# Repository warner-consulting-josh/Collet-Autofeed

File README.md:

# Collet-Autofeed

Automation of Collets on the Tormach Slant Pro lathe using a custom tooling block, individually addressable coolant lines controlled by an [UnexpectedMaker ProS3](https://esp32s3.com/pros3.html) and ui_hooks.py, and custom G-code for auto stock advance.

## Description

This project uses the uihooks.py [Plugin controller](http://xoomspeed.com/CNC/pathpilot/plugins/uihooks.htm) created by David Loomes at XoomSpeed, to run custom python code for interacting with a ProS3 microcontroller which in turn controls solenoids to direct the coolant stream to the currently active tool. We've also implemented custom G-code to auto advance the stock after each part with a GUI for inputting the stock length at the beginning of the run. (The stock input GUI only works on earlier versions of PathPilot, but it is not reequired for the rest of the system to function)
The hardware includes a custom tooling block, a manifold for the solenoids, a main board with the microcontroller and relays, a connector board to break out the relay lines, and enclosures for both boards.

## Getting Started

### Dependencies

* PathPilot V2
* PathPilot Plugins by [Xoomspeed](http://xoomspeed.com/CNC/pathpilot/plugins.htm)

### Installing

* Follow the instructions from [Xoomspeed](http://xoomspeed.com/CNC/pathpilot/plugins.htm) for intstalling the PathPilot Plugin framework
   * The specific plugin for running the coolant controller is [here:](https://github.com/warner-consulting-josh/Collet-Autofeed/blob/main/PathPilot%20Python/ProS3Cool_plugin.py)
* The circuitpython code that runs on the microcontroller is [here:](https://github.com/warner-consulting-josh/Collet-Autofeed/blob/main/ProS3%20CircuitPython/code.py)
   * Note that the file must be named code.py for the microcontroller using circuitpython to recognize and run it 

### Circuit Boards

* Gerber files for ordering the circuit boards are [here:](https://github.com/warner-consulting-josh/Collet-Autofeed/tree/main/KiCAD/Addressable_Coolant_Controller/gerber_to_order)
* boards were designed in KiCAD using a multi-board workflow with [KiKit](https://yaqwsx.github.io/KiKit/v1.4/multiboard/)

## Authors

Contributors names and contact info

Josh Warner  
joshua@warner-consulting.com

## Version History

* 1.0.0
    * Initial Release

## License

This project is licensed under the [GPL-3.0-only](https://opensource.org/license/gpl-3-0) License

## Acknowledgments

Inspiration, code snippets, etc.
* [XoomSpeed](http://xoomspeed.com/index.htm)
* [KiKit](https://yaqwsx.github.io/KiKit/v1.4/)
* [awesome-readme](https://github.com/matiassingers/awesome-readme)
* [PurpleBooth](https://gist.github.com/PurpleBooth/109311bb0361f32d87a2)
* [dbader](https://github.com/dbader/readme-template)
* [zenorocha](https://gist.github.com/zenorocha/4526327)
* [fvcproductions](https://gist.github.com/fvcproductions/1bfc2d4aecb01a834b46)

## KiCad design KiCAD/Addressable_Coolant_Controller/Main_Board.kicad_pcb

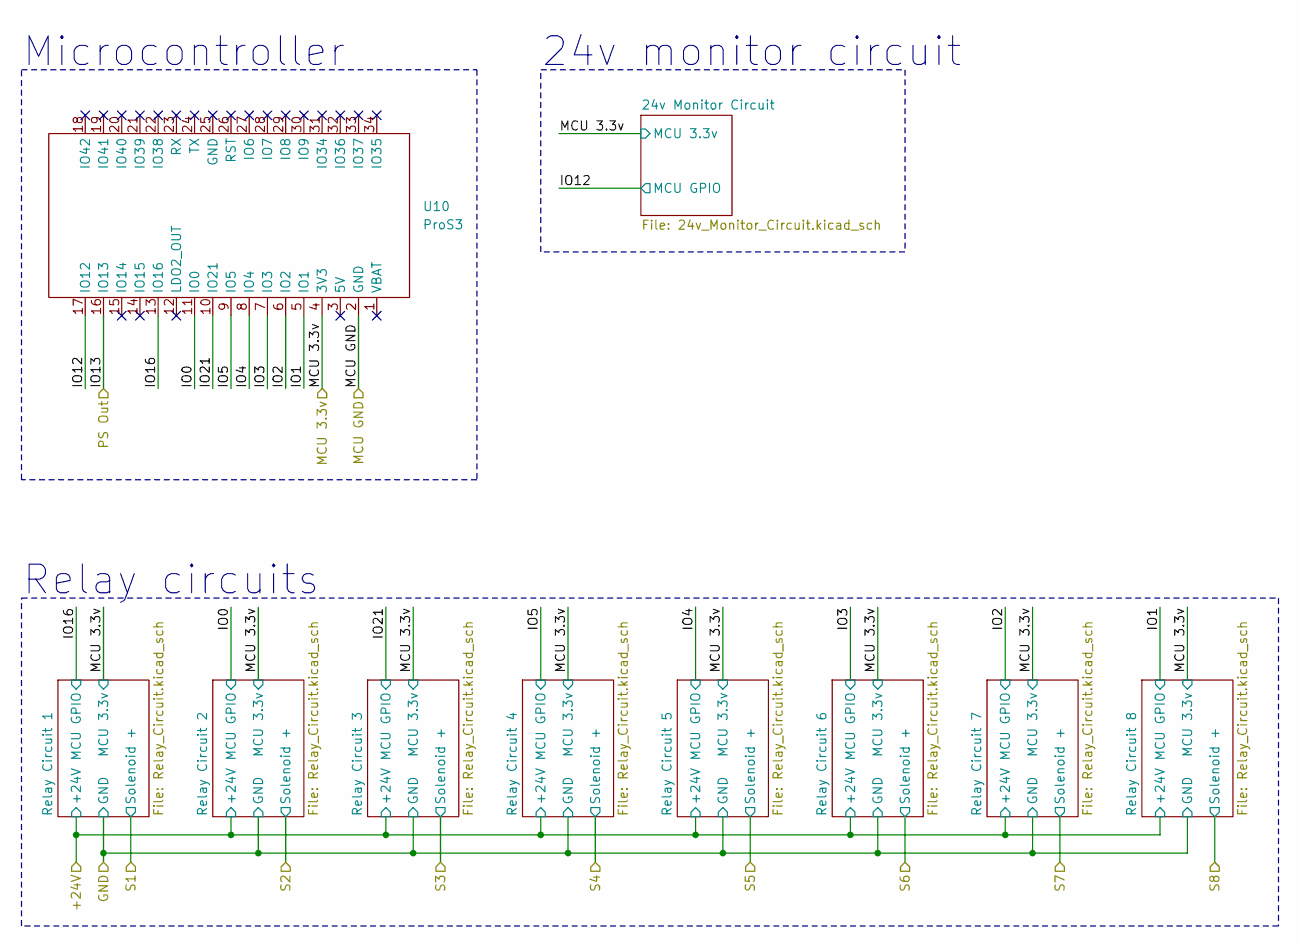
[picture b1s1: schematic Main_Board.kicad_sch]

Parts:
U10: ProS3; ProS3_TH

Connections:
/Main_Board/IO0: U10.11 (IO0); also elsewhere on the board
/Main_Board/IO1: U10.5 (IO1); also elsewhere on the board
/Main_Board/IO2: U10.6 (IO2); also elsewhere on the board
/Main_Board/IO3: U10.7 (IO3); also elsewhere on the board
/Main_Board/IO4: U10.8 (IO4); also elsewhere on the board
/Main_Board/IO5: U10.9 (IO5); also elsewhere on the board
/Main_Board/IO12: U10.17 (IO12); also elsewhere on the board
/Main_Board/IO13: U10.16 (IO13); also elsewhere on the board
/Main_Board/IO16: U10.13 (IO16); also elsewhere on the board
/Main_Board/IO21: U10.10 (IO21); also elsewhere on the board
/Main_Board/MCU 3.3v: U10.4 (3V3); also elsewhere on the board
/Main_Board/MCU GND: U10.2 (GND); also elsewhere on the board

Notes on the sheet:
Microcontroller
24v monitor circuit
Relay circuits

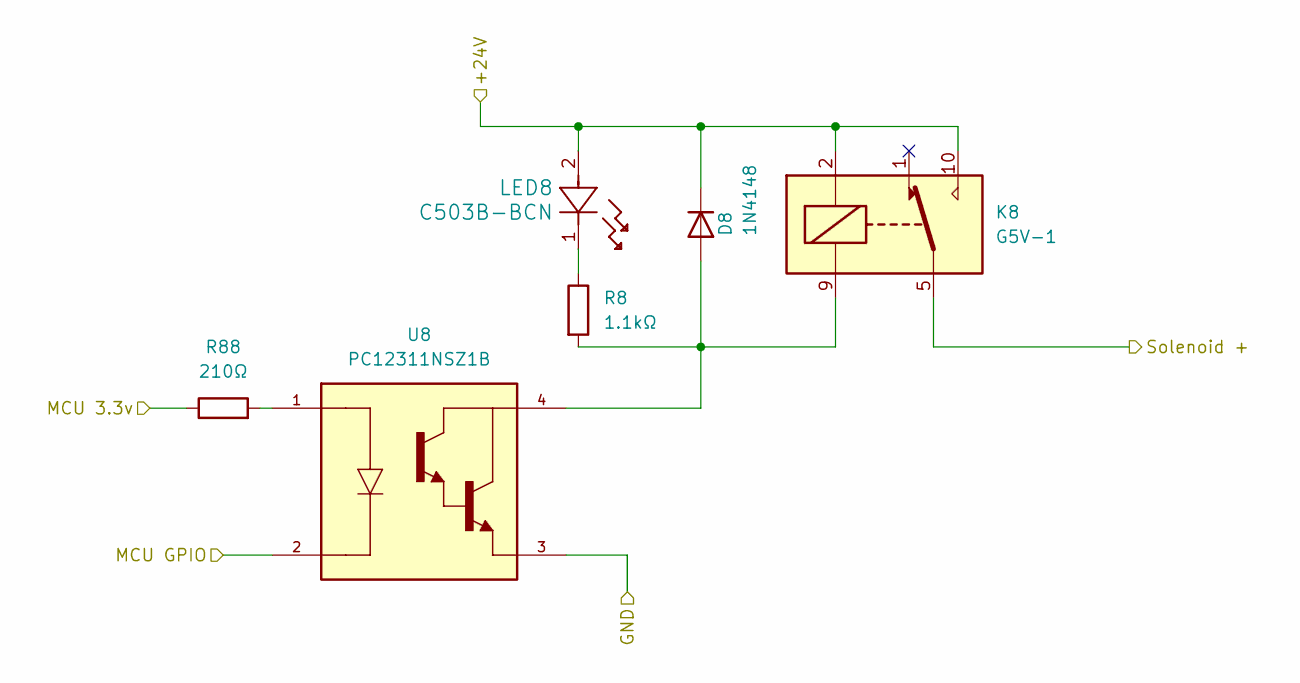
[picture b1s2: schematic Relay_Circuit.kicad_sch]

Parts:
D8: 1N4148; D_DO-35_SOD27_P7.62mm_Horizontal-JW
K8: G5V-1; Relay_SPDT_Omron_G5V-1
LED8: C503B-BCN; C503B_BCN_CV0Z0461
R8: 1.1kΩ; R_Axial_DIN0204_L3.6mm_D1.6mm_P5.08mm_Horizontal-JW
R88: 210Ω; R_Axial_DIN0204_L3.6mm_D1.6mm_P5.08mm_Horizontal-JW
U8: PC12311NSZ1B; Mouser Part Number 852-PC12311NSZ1B

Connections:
+24V: D8.1 (K), K8.2, K8.10, LED8.2; also elsewhere on the board
/Main_Board/IO1: U8.2; also elsewhere on the board
/Main_Board/MCU 3.3v: R88.1; also elsewhere on the board
/Main_Board/S8: K8.5, K8.6; also elsewhere on the board
GND: U8.3; also elsewhere on the board
unnamed: D8.2 (A), K8.9, R8.2, U8.4
unnamed: LED8.1, R8.1
unnamed: R88.2, U8.1

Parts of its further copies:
D1, D2, D3, D4, D5, D6, D7: 1N4148; D_DO-35_SOD27_P7.62mm_Horizontal-JW
K1, K2, K3, K4, K5, K6, K7: G5V-1; Relay_SPDT_Omron_G5V-1
LED1, LED2, LED3, LED4, LED5, LED6, LED7: C503B-BCN; C503B_BCN_CV0Z0461
R1, R2, R3, R4, R5, R6, R7: 1.1kΩ; R_Axial_DIN0204_L3.6mm_D1.6mm_P5.08mm_Horizontal-JW
R11, R22, R33, R44, R55, R66, R77: 210Ω; R_Axial_DIN0204_L3.6mm_D1.6mm_P5.08mm_Horizontal-JW
U1, U2, U3, U4, U5, U6, U7: PC12311NSZ1B; Mouser Part Number 852-PC12311NSZ1B

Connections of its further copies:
+24V: D1.1 (K), D2.1 (K), D3.1 (K), D4.1 (K), D5.1 (K), D6.1 (K), D7.1 (K), K1.2, K1.10, K2.2, K2.10, K3.2, K3.10, K4.2, K4.10, K5.2, K5.10, K6.2, K6.10, K7.2, K7.10, LED1.2, LED2.2, LED3.2, LED4.2, LED5.2, LED6.2, LED7.2; also elsewhere on the board
/Main_Board/IO0: U2.2; also elsewhere on the board
/Main_Board/IO2: U7.2; also elsewhere on the board
/Main_Board/IO3: U6.2; also elsewhere on the board
/Main_Board/IO4: U5.2; also elsewhere on the board
/Main_Board/IO5: U4.2; also elsewhere on the board
/Main_Board/IO16: U1.2; also elsewhere on the board
/Main_Board/IO21: U3.2; also elsewhere on the board
/Main_Board/MCU 3.3v: R11.1, R22.1, R33.1, R44.1, R55.1, R66.1, R77.1; also elsewhere on the board
/Main_Board/S1: K1.5, K1.6; also elsewhere on the board
/Main_Board/S2: K2.5, K2.6; also elsewhere on the board
/Main_Board/S3: K3.5, K3.6; also elsewhere on the board
/Main_Board/S4: K4.5, K4.6; also elsewhere on the board
/Main_Board/S5: K5.5, K5.6; also elsewhere on the board
/Main_Board/S6: K6.5, K6.6; also elsewhere on the board
/Main_Board/S7: K7.5, K7.6; also elsewhere on the board
GND: U1.3, U2.3, U3.3, U4.3, U5.3, U6.3, U7.3; also elsewhere on the board
unnamed: D1.2 (A), K1.9, R1.2, U1.4
unnamed: D2.2 (A), K2.9, R2.2, U2.4
unnamed: D3.2 (A), K3.9, R3.2, U3.4
unnamed: D4.2 (A), K4.9, R4.2, U4.4
unnamed: D5.2 (A), K5.9, R5.2, U5.4
unnamed: D6.2 (A), K6.9, R6.2, U6.4
unnamed: D7.2 (A), K7.9, R7.2, U7.4
unnamed: LED1.1, R1.1
unnamed: LED2.1, R2.1
unnamed: LED3.1, R3.1
unnamed: LED4.1, R4.1
unnamed: LED5.1, R5.1
unnamed: LED6.1, R6.1
unnamed: LED7.1, R7.1
unnamed: R11.2, U1.1
unnamed: R22.2, U2.1
unnamed: R33.2, U3.1
unnamed: R44.2, U4.1
unnamed: R55.2, U5.1
unnamed: R66.2, U6.1
unnamed: R77.2, U7.1

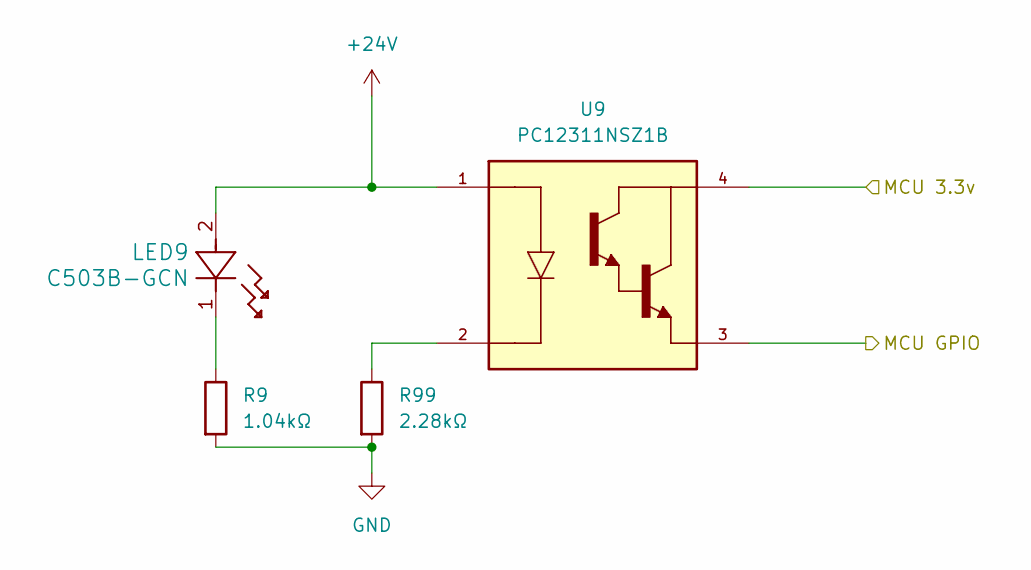
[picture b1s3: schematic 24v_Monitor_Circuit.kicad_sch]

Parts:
LED9: C503B-GCN; C503B_GCN_CY0C0792
R9: 1.04kΩ; R_Axial_DIN0204_L3.6mm_D1.6mm_P5.08mm_Horizontal-JW
R99: 2.28kΩ; R_Axial_DIN0204_L3.6mm_D1.6mm_P5.08mm_Horizontal-JW
U9: PC12311NSZ1B; Mouser Part Number 852-PC12311NSZ1B

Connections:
+24V: LED9.2, U9.1; also elsewhere on the board
/Main_Board/IO12: U9.3; also elsewhere on the board
/Main_Board/MCU 3.3v: U9.4; also elsewhere on the board
GND: R9.2, R99.2; also elsewhere on the board
unnamed: LED9.1, R9.1
unnamed: R99.1, U9.2

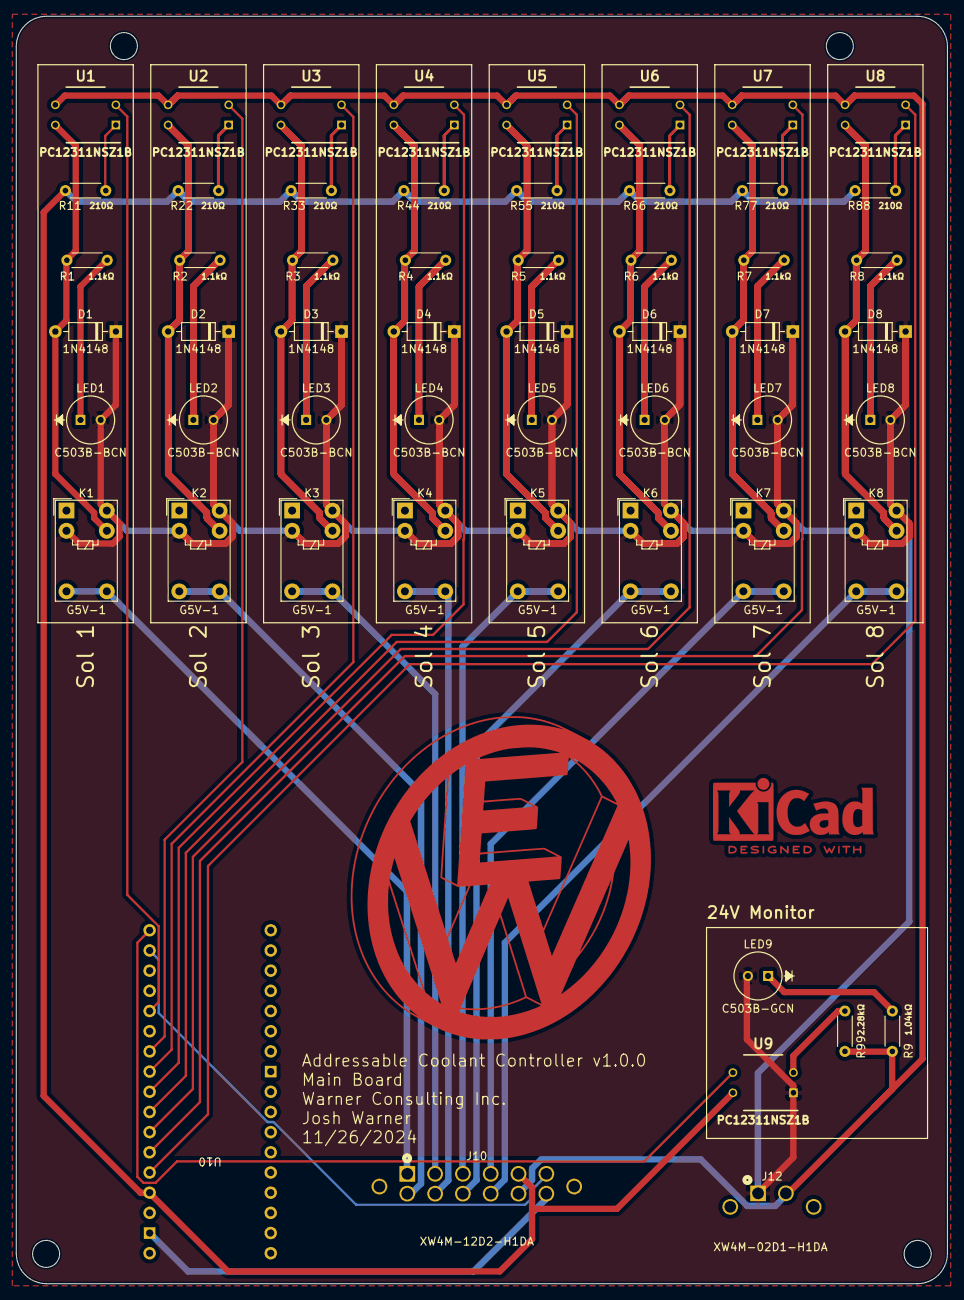
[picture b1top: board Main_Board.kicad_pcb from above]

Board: 2 copper layers, 117.2 x 159.5 mm, 56 parts (0 on the bottom side), 48 nets.

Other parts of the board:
J10: XW4M-12D2-H1DA; xw4m-12d2-h1da
J12: XW4M-02D1-H1DA; xw4m-02d1-h1da
Main_Board: Board

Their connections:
+24V: J12.1; also elsewhere on the board
/Main_Board/IO13: J10.6; also elsewhere on the board
/Main_Board/MCU 3.3v: J10.5; also elsewhere on the board
/Main_Board/MCU GND: J10.12; also elsewhere on the board
/Main_Board/S1: J10.1; also elsewhere on the board
/Main_Board/S2: J10.7; also elsewhere on the board
/Main_Board/S3: J10.2; also elsewhere on the board
/Main_Board/S4: J10.8; also elsewhere on the board
/Main_Board/S5: J10.3; also elsewhere on the board
/Main_Board/S6: J10.9; also elsewhere on the board
/Main_Board/S7: J10.4; also elsewhere on the board
/Main_Board/S8: J10.10; also elsewhere on the board
GND: J10.11, J12.2; also elsewhere on the board

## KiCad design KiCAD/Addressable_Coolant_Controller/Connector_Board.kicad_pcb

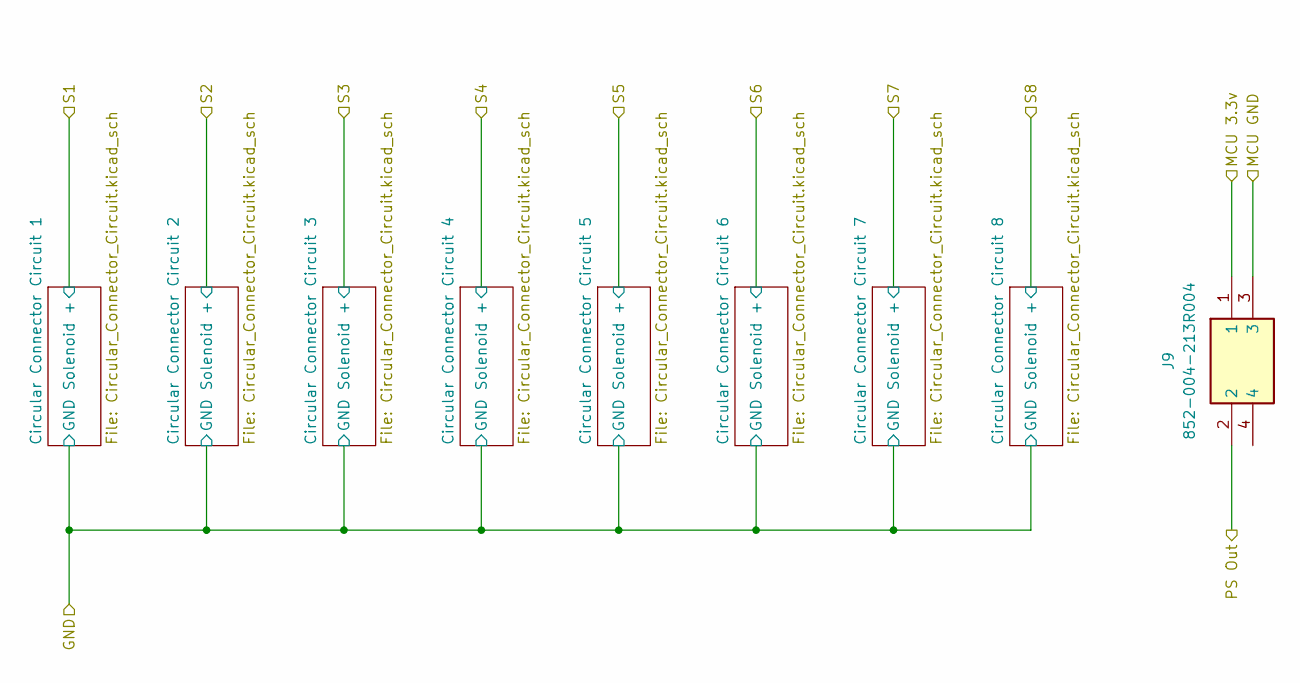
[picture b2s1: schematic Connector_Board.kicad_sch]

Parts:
J9: 852-004-213R004; 852004213R004; Manufacturer_Part_Number 852-004-213R004

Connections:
/Connector_Board/MCU 3.3v: J9.1; also elsewhere on the board
/Connector_Board/MCU GND: J9.3; also elsewhere on the board
/Connector_Board/PS Out: J9.2; also elsewhere on the board

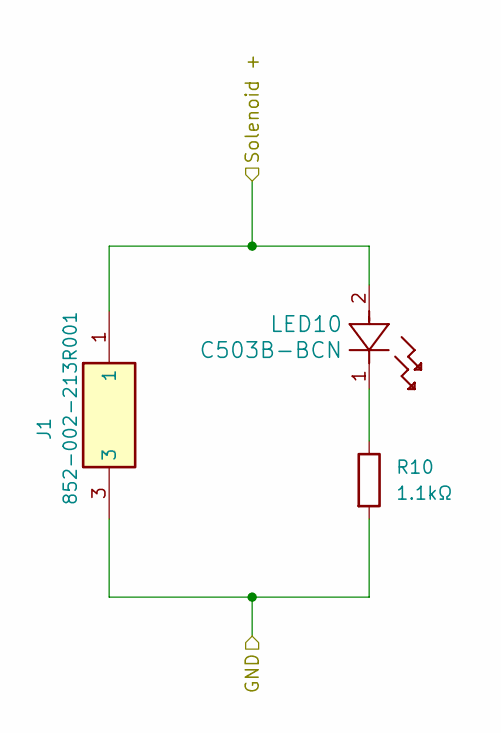
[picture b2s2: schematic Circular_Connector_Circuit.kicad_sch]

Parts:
J1: 852-002-213R001; Mouser Part Number 636-852-002-213R001
LED10: C503B-BCN; C503B_BCN_CV0Z0461
R10: 1.1kΩ; R_Axial_DIN0204_L3.6mm_D1.6mm_P5.08mm_Horizontal-JW

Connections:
/Connector_Board/GND: J1.3, R10.2; also elsewhere on the board
/Connector_Board/S1: J1.1, LED10.2; also elsewhere on the board
unnamed: LED10.1, R10.1

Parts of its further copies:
J2, J3, J4, J5, J6, J7, J8: 852-002-213R001; Mouser Part Number 636-852-002-213R001
LED20, LED30, LED40, LED50, LED60, LED70, LED80: C503B-BCN; C503B_BCN_CV0Z0461
R20, R30, R40, R50, R60, R70, R80: 1.1kΩ; R_Axial_DIN0204_L3.6mm_D1.6mm_P5.08mm_Horizontal-JW

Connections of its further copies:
/Connector_Board/GND: J2.3, J3.3, J4.3, J5.3, J6.3, J7.3, J8.3, R20.2, R30.2, R40.2, R50.2, R60.2, R70.2, R80.2; also elsewhere on the board
/Connector_Board/S2: J2.1, LED20.2; also elsewhere on the board
/Connector_Board/S3: J3.1, LED30.2; also elsewhere on the board
/Connector_Board/S4: J4.1, LED40.2; also elsewhere on the board
/Connector_Board/S5: J5.1, LED50.2; also elsewhere on the board
/Connector_Board/S6: J6.1, LED60.2; also elsewhere on the board
/Connector_Board/S7: J7.1, LED70.2; also elsewhere on the board
/Connector_Board/S8: J8.1, LED80.2; also elsewhere on the board
unnamed: LED20.1, R20.1
unnamed: LED30.1, R30.1
unnamed: LED40.1, R40.1
unnamed: LED50.1, R50.1
unnamed: LED60.1, R60.1
unnamed: LED70.1, R70.1
unnamed: LED80.1, R80.1

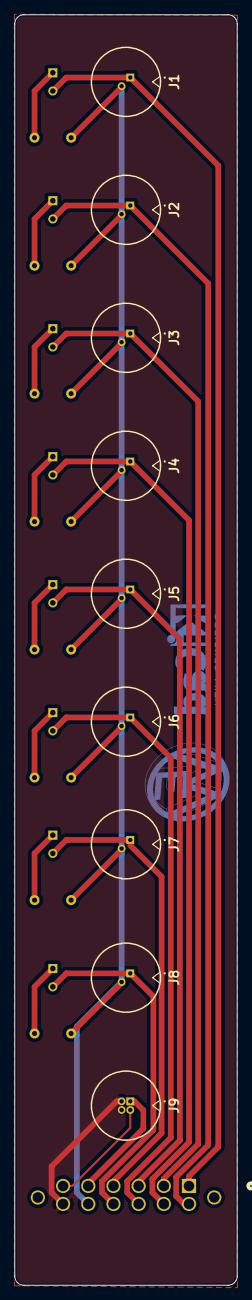
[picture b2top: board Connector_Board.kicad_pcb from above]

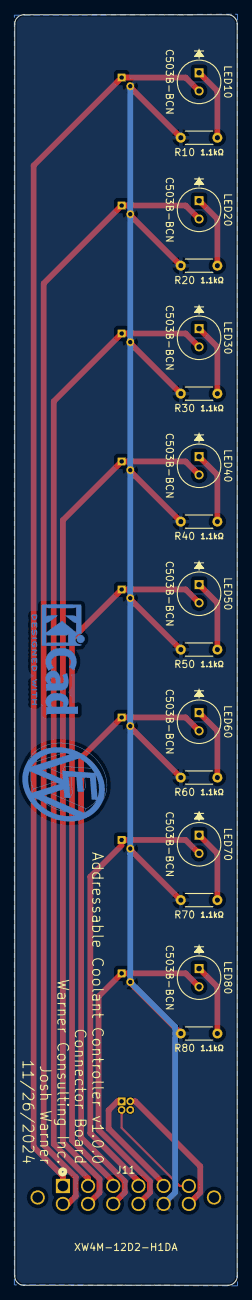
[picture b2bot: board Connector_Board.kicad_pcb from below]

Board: 2 copper layers, 30.9 x 176.5 mm, 27 parts (17 on the bottom side), 20 nets.

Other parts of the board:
Connector_Board: Board
J11: XW4M-12D2-H1DA; xw4m-12d2-h1da

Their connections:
/Connector_Board/GND: J11.11; also elsewhere on the board
/Connector_Board/MCU 3.3v: J11.5; also elsewhere on the board
/Connector_Board/MCU GND: J11.12; also elsewhere on the board
/Connector_Board/PS Out: J11.6; also elsewhere on the board
/Connector_Board/S1: J11.1; also elsewhere on the board
/Connector_Board/S2: J11.7; also elsewhere on the board
/Connector_Board/S3: J11.2; also elsewhere on the board
/Connector_Board/S4: J11.8; also elsewhere on the board
/Connector_Board/S5: J11.3; also elsewhere on the board
/Connector_Board/S6: J11.9; also elsewhere on the board
/Connector_Board/S7: J11.4; also elsewhere on the board
/Connector_Board/S8: J11.10; also elsewhere on the board

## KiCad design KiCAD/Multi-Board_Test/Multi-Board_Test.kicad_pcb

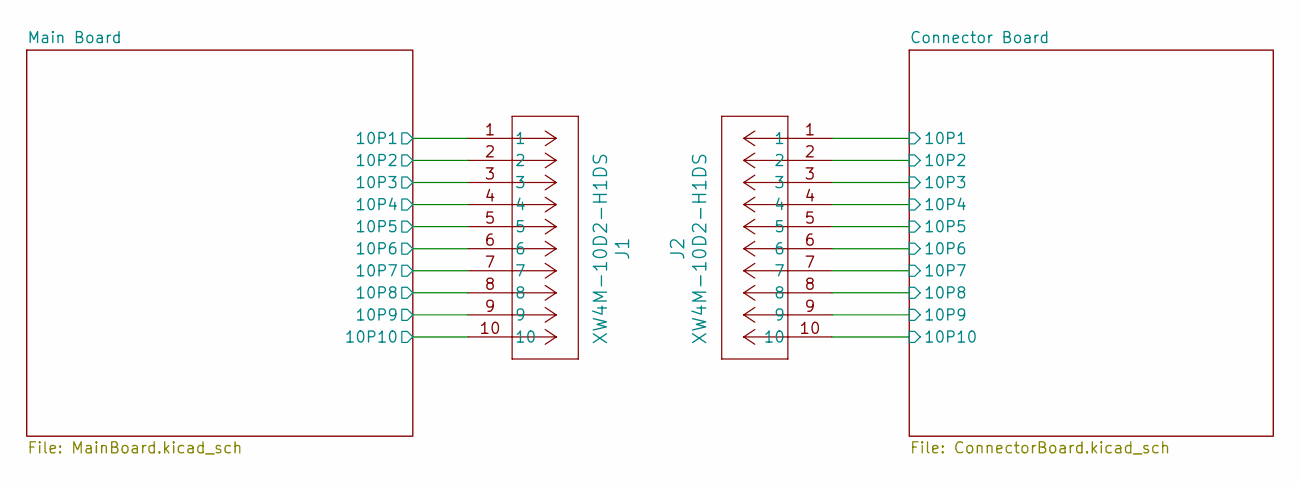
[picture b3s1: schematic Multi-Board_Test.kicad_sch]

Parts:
J1, J2: XW4M-10D2-H1DS; xw4m-10d2-h1ds

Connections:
/Connector Board/10P1: J2.1; also elsewhere on the board
/Connector Board/10P2: J2.2; also elsewhere on the board
/Connector Board/10P3: J2.3; also elsewhere on the board
/Connector Board/10P4: J2.4; also elsewhere on the board
/Connector Board/10P5: J2.5; also elsewhere on the board
/Connector Board/10P6: J2.6; also elsewhere on the board
/Connector Board/10P7: J2.7; also elsewhere on the board
/Connector Board/10P8: J2.8; also elsewhere on the board
/Connector Board/GND: J2.9, J2.10; also elsewhere on the board
/Main Board/10P1: J1.1; also elsewhere on the board
/Main Board/10P2: J1.2; also elsewhere on the board
/Main Board/10P3: J1.3; also elsewhere on the board
/Main Board/10P4: J1.4; also elsewhere on the board
/Main Board/10P5: J1.5; also elsewhere on the board
/Main Board/10P6: J1.6; also elsewhere on the board
/Main Board/10P7: J1.7; also elsewhere on the board
/Main Board/10P8: J1.8; also elsewhere on the board
/Main Board/GND: J1.9, J1.10; also elsewhere on the board

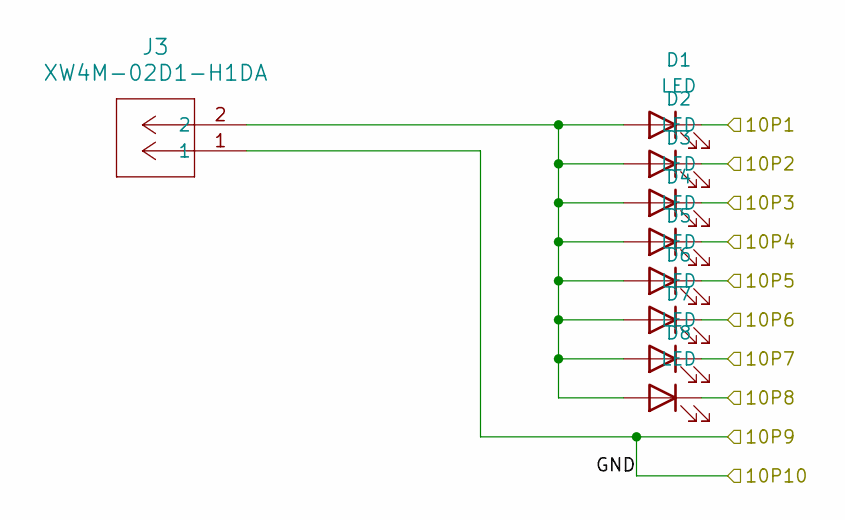
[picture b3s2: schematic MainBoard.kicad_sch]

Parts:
D1, D2, D3, D4, D5, D6, D7, D8: LED; LED_BL-FL7680RGB
J3: XW4M-02D1-H1DA; xw4m-02d1-h1da

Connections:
/Main Board/10P1: D1.1 (K); also elsewhere on the board
/Main Board/10P2: D2.1 (K); also elsewhere on the board
/Main Board/10P3: D3.1 (K); also elsewhere on the board
/Main Board/10P4: D4.1 (K); also elsewhere on the board
/Main Board/10P5: D5.1 (K); also elsewhere on the board
/Main Board/10P6: D6.1 (K); also elsewhere on the board
/Main Board/10P7: D7.1 (K); also elsewhere on the board
/Main Board/10P8: D8.1 (K); also elsewhere on the board
/Main Board/GND: J3.1; also elsewhere on the board
unnamed: D1.2 (A), D2.2 (A), D3.2 (A), D4.2 (A), D5.2 (A), D6.2 (A), D7.2 (A), D8.2 (A), J3.2

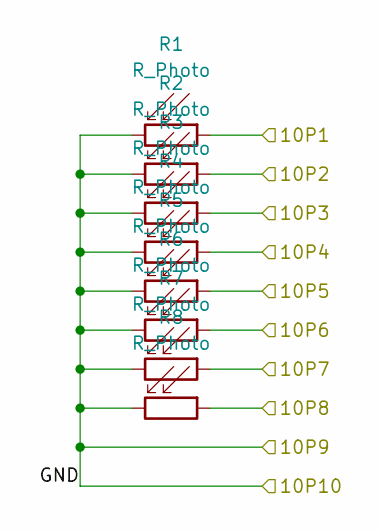
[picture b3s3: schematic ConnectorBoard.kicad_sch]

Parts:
R1, R2, R3, R4, R5, R6, R7, R8: R_Photo; R_Axial_DIN0204_L3.6mm_D1.6mm_P1.90mm_Vertical

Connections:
/Connector Board/10P1: R1.1; also elsewhere on the board
/Connector Board/10P2: R2.1; also elsewhere on the board
/Connector Board/10P3: R3.1; also elsewhere on the board
/Connector Board/10P4: R4.1; also elsewhere on the board
/Connector Board/10P5: R5.1; also elsewhere on the board
/Connector Board/10P6: R6.1; also elsewhere on the board
/Connector Board/10P7: R7.1; also elsewhere on the board
/Connector Board/10P8: R8.1; also elsewhere on the board
/Connector Board/GND: R1.2, R2.2, R3.2, R4.2, R5.2, R6.2, R7.2, R8.2; also elsewhere on the board

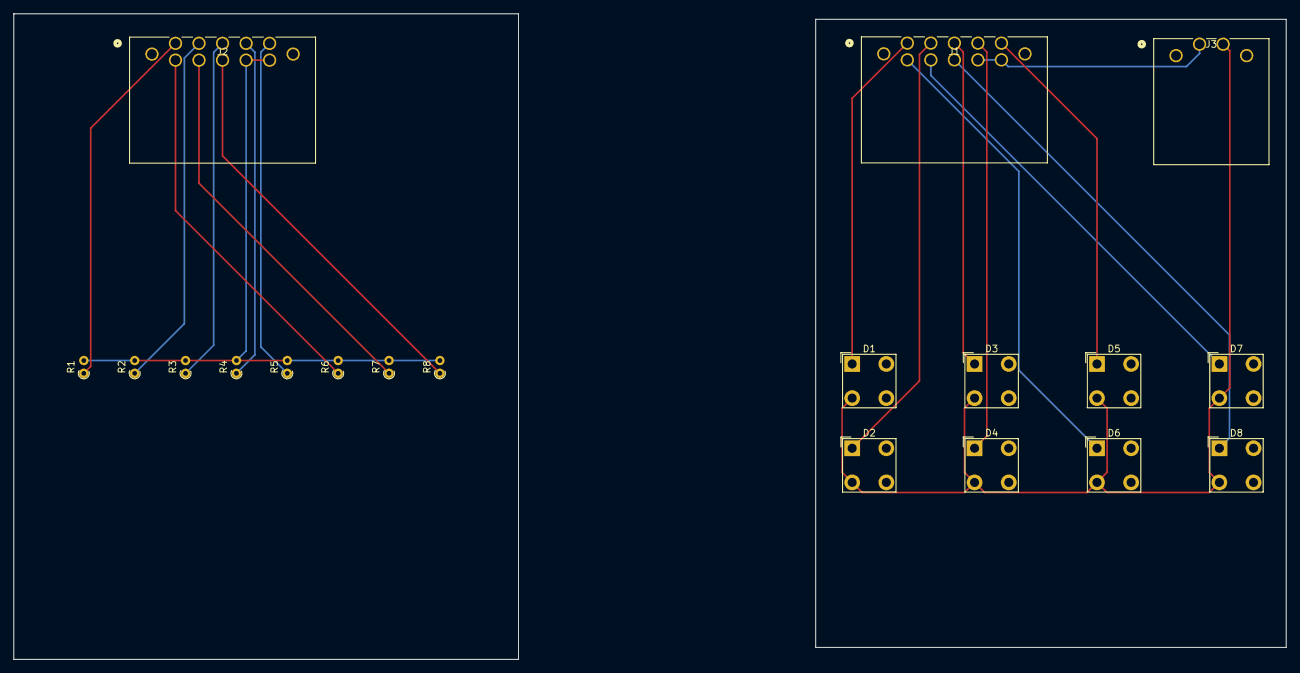
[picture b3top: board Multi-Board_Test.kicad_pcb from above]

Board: 2 copper layers, 189.2 x 96.0 mm, 21 parts (0 on the bottom side), 19 nets.

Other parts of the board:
B1, B2: Board

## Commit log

2024-01-22 Create Project Log
    Added project log with details of what I did each day so that if I need to revert things (other than code) it's easier and so that I know where to pick up each day
2024-01-22 Update and rename Project Log to Project Log.md
    Fixed markdown
2024-01-23 Added Pathpilot Python files
    [ui_hooks.py](http://xoomspeed.com/CNC/pathpilot/plugins/uihooks.htm)
    ToolPrint_plugin.py - First test of creating plugin code to identify current tool number
2024-01-23 Update and rename ToolPrint_plugin.py to PathPilot Python/ToolPrint_plugin.py
    Moved to PathPilot Python folder
2024-01-23 Update and rename ui_hooks.py to PathPilot Python/ui_hooks.py
    Moved to PathPilot Python folder
2024-01-23 Delete PathPilot Python/dummy.txt
    Removed dummy file from PathPilot Python
2024-01-23 Update Project Log.md
    Updated log for 01/23/2024
2024-01-23 Update README.md
    Changed TinyS3 to ProS3 and added link.
2024-01-25 Implemented 2 way serial communication
    Implemented serial communication on the device side. Needed to add some error handling code and especially needed to disable the modemmanager service in linux
2024-01-25 Update Notes.md
    Spelling fix
2024-01-25 Update Notes.md
    Added section for electronics
2024-01-27 Uploaded KiCAD files
2024-02-05 Update code.py
    Added watchdog code and reset reason code.
2024-02-08 Update code.py
    Got relay control working. Need to fix LED blink code. Removed watchdog for testing purposes.
2024-02-12 Rename KiCAD/KiCAD.gitignore to .gitignore
2024-02-12 Added KiCAD files to repository
2024-02-12 Delete KiCAD/ColletAutoFeed_RelayBoard 20240208.zip
    Remove old zip files
2024-02-12 Delete KiCAD/ColletAutoFeed_RelayBoard 20240209.zip
    Removed old zip files
2024-02-12 Delete KiCAD/ColletAutoFeed_RelayBoard.zip
    Removed old zip files
2024-02-12 Added 24v Monitor Circuit
    Added hierarchical sheet with 24v monitor circuit. Added 4 pin power connector for 24v input. Same family connector as ribbon cable connector for relay to solenoid connections out to daughter board.
2024-02-13 Ran Annotation and ERC
    Annotated and ran Electronics Rules Checker. Started assigning footprints and appropriate step files to said footprints. Added custom KiCAD library folder to Github.
2024-02-14 Removed Custom Libraries
    Setting up for using git submodule
2024-02-14 Added Warner-Consulting-Libraries submodule
2024-02-14 Removed improperly spelled submodule
2024-02-14 Added Warner-Consulting-Libraries submodule
    Correctly spelled this time
2024-02-14 Added ProS3 symbol, footprint, and step file from submodule
2024-02-14 Updated submodule commit
2024-02-15 Update Warner-Consulting-Libraries
2024-02-15 Switched to TE AMP-Latch connector
    Removed Wurth ribbon cable connector and replaced with TE AMP-Latch connector after physically evaluating both.
2024-02-15 Updating submodule commit
2024-02-15 Assigned footprint to pin header
2024-02-15 Added borders and labels to schematic
2024-02-17 Update submodule comit
2024-02-17 Started PCB layout
2024-02-17 Updating submodule comit
2024-02-17 Changed to tht LEDs and added LED to power monitor circuit
2024-02-20 Started routing
2024-02-20 Continued routing
2024-02-20 Added ground and power planes
2024-02-21 Continued working on routing
2024-02-25 Updated resistor footprints to include values
2024-02-29 Started working on display code
    Branched and removed all code except display code until display code is functioning.
2024-03-01 Combined display code with serial read code
    Successfully displayed current tool number on OLED display using Mu, Pathpilot Virtual Machine, and actual lathe.
2024-03-06 Combined 2 pin power input into ribbon cable
2024-09-03 Update Project Log.md
    Updated for work done 09/03/2024
2024-09-03 Update Notes.md
    Added notes on remapping custom m-codes
2024-10-11 Scaled Text on screen
    Scaled text on screen to 2x to be more readable.
2024-10-14 Update .gitignore to include .lck (kicad lock files)
2024-10-14 Fixing untracked changes issue
2024-10-15 Replaced ribbon cable connector with 10-pin molex
2024-10-17 Update Notes.md
    add info on fixing submodule sync error
2024-10-17 Updating submodule
2024-10-17 Updated board to new size
    Updated board outline, stripped all old routing, added 2 pin omron power connector
2024-10-22 Placed components and routed traces on PCB
    Placed components and completed initial routing. Still need to add power and ground planes and figure out silkscreen.
2024-10-23 updating libraries with through hole opto-isolator
2024-10-23 Replaced opto-isolator with through hole version
2024-10-24 Added rectangle representing screen
2024-10-25 Replaced remaining opto-isolator and started silkscreen
2024-10-25 Updating libraries
2024-10-25 Fixed Silkscreen Labels for Components
2024-10-28 Shortened LED legs and updated the submodule to reflect
2024-10-28 Added logo footprint to library
2024-10-28 Update Notes.md
    Added info on adding custom graphics to KiCAD silkscreen
2024-10-28 Added Logo to silkscreen
2024-10-29 Added zones and labels to Silkscreen
2024-10-30 Renamed to Addressable Coolant Controller v1.0.0
2024-10-30 Changed project name to Addressable Coolant Controller
2024-10-31 Created Multi-Board Test Project
2024-11-11 Worked on multi board workflow
2024-11-11 updating libraries submodule
2024-11-11 Changing project name to "Addressable_Coolant_Controller"
    Removed spaces from project name to avoid issues with file system wonkiness.
2024-11-11 Update .gitmodules to reflect KiCAD project name change
2024-11-11 Removing broken submodule
2024-11-11 Adding fixed submodule
2024-11-12 Updating KiCAD project to multi-board structure
2024-11-14 Updating library footprint
2024-11-14 Updating library footprint with step file
2024-11-14 Updating omron 2-pin footprint
2024-11-14 Updating omron footprints
2024-11-14 Updating wiring positions to match 12 pin connector
2024-11-14 Updating omron sybols to point at footprints
2024-11-14 Added voltage divider and changed to 12 pin connectors
2024-11-14 Fixed broken netclasses, removed voltage divider circuit
2024-11-19 Added hierarchical labels to connector board
2024-11-22 Updating NorComp 2-pin library
2024-11-22 Adding NorComp 4-pin library
2024-11-22 Updating NorComp Libraries
2024-11-22 Added second board outline and circular connectors
2024-11-22 Updating PC123 Footprint
2024-11-25 Routed connector PCB and fixed components designators
2024-11-26 Added LEDs to connector board, and moved to hierarchical sheet
2024-11-26 Updating Cree LED footprints
2024-11-26 Update Cree LED Symbols
2024-11-26 Updating Cree LED symbols
2024-11-26 Updating Cree LED footprints with STEP files
2024-11-26 Updating PC123 footprint with STEP file
2024-11-26 Finished board layout
2024-11-26 Removing overhanging silkscreen from Omron footprints
2024-11-26 updating 2-pin Omron with square pin 1
2024-11-27 Finalized board design and exported for ordering
2024-12-02 Created IBOM
2024-12-16 Mapped pins in code to board, added power monitor code
2025-01-02 Added Code for Pressure Sensor
2025-01-10 Refactored code to use state machine in Plugin and Microcontroller
2025-01-20 Added power and tool error checks
2025-01-21 Converted ADC reading to PSI
2025-01-22 Added plugin side connection error gcode pause
2026-01-29 Update Notes.md
    Added instructions for dealing with untracked files error in submodule
2026-01-29 Update Notes.md
    added info about global vs project specific library
2026-01-29 Update Notes.md
    added info for detached HEAD
